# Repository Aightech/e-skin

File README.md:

# E-Skin

A bioinspired electronic skin system for robotic applications, combining FSR (force-sensing resistor) arrays and accelerometer arrays.

## Overview

The electronic board uses two multiplexers and two 16-channel ADCs to read the FSRs. The multiplexers select the row or column of the FSR array, while the ADCs read the sensor values. A Teensy 4.1 controls the multiplexers and ADCs and sends data to the computer via USB or Ethernet.

**Operation modes:**
- **Single mode**: Connect one FSR array with up to 32x32 sensors
- **Dual mode**: Connect two FSR arrays with up to 16x16 sensors each

**Sampling rate:** ~400 KHz/channel (1562.5 Hz for a 16x16 array)

## Project Structure

```
e-skin/
├── host/           # C++/Qt host application
│   ├── src/        # Source code (main.cpp)
│   └── lib/        # Git submodules (com_client, built_lsl)
├── src/            # Teensy firmware
│   └── Eskin/      # Main production firmware
├── models/         # KiCAD PCB designs
│   ├── KiCAD/              # Main control board (MUX + ADC)
│   ├── customSquare16x16/  # 16x16 FSR array
│   ├── customSquare8x8/    # 8x8 FSR array
│   ├── LIS2DH_array/       # LIS2DH accelerometer array
│   ├── KX134_array/        # KX134 accelerometer array
│   └── inskinacc/          # In-skin accelerometer
└── script/         # Python/MATLAB data acquisition scripts
```

## Requirements

### Host Application
- CMake 3.3+
- Qt6 (Core, Widgets, PrintSupport)
- C++11 compiler

### Firmware
- Arduino IDE or PlatformIO
- Teensy 4.1 board support

### Python Scripts
- Python 3.x
- Dependencies: `pip install -r script/requirements.txt`

## Building

### Host Application

```bash
cd host
mkdir build && cd build
cmake .. && make
./FSR_array -h  # Show usage
```

### Firmware

Upload `src/Eskin/Eskin.ino` to Teensy 4.1 using Arduino IDE or PlatformIO.

- Board: Teensy 4.1
- Port: `/dev/ttyACM0` (Linux) or `COMx` (Windows)

### Python Data Recorder

```bash
pip install -r script/requirements.txt
python script/record.py <port> <array_size>
# Example: python script/record.py /dev/ttyACM0 16
```

## Communication Protocol

- **Serial**: 500000 baud
- **Ethernet**: TCP port 5000
- **Command format**: 1 byte (2 MSB = mode, 6 LSB = array size)
  - Mode 0: Request 1 FSR array
  - Mode 1: Request 2 FSR arrays
  - Mode 2: Request 1 ACC array
  - Mode 3: Request 1 ACC array + 2 FSR arrays
- **Response**: 4-byte timestamps + uint16_t sensor data

## Submodule Dependencies

- [built_lsl](host/lib/built_lsl/README.md) - Lab Streaming Layer integration
- [com_client](host/lib/com_client/README.md) - Serial/TCP communication library

Initialize submodules:
```bash
git submodule update --init --recursive
```

## Example

See [main.cpp](host/src/main.cpp) for an example of how to use the communication library.

## Contributing

See [CONTRIBUTING.md](CONTRIBUTING.md) for details on our code of conduct and the process for submitting pull requests.

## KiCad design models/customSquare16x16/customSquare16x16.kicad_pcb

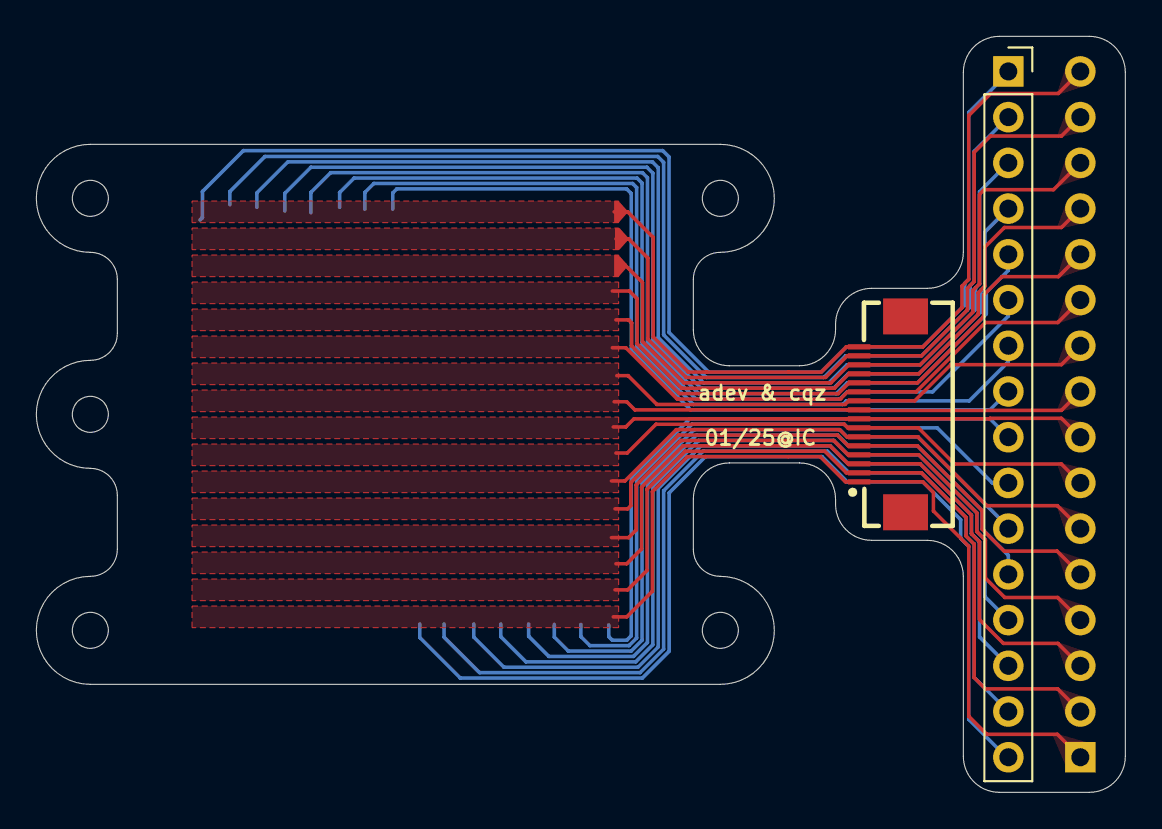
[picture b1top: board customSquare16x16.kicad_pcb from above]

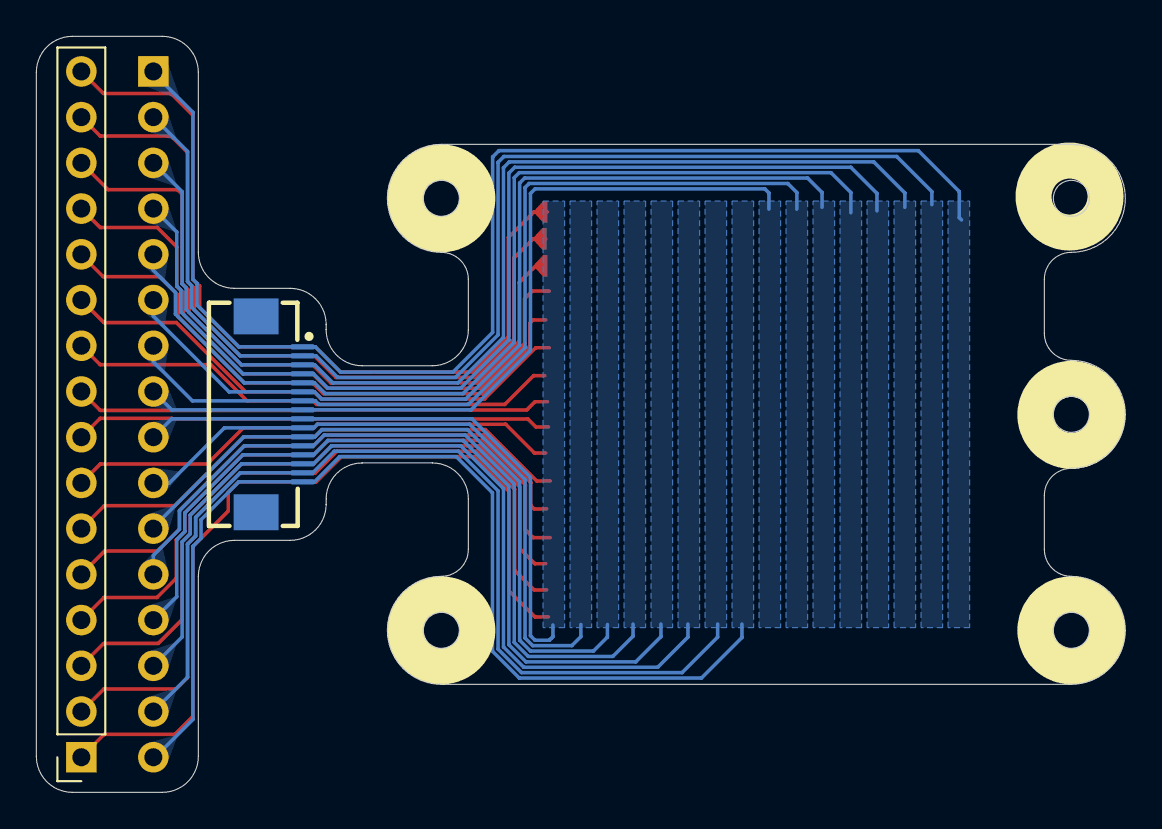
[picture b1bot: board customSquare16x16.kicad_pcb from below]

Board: 2 copper layers, 60.5 x 42.0 mm, 4 parts (2 on the bottom side), 32 nets.

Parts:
FPC1, FPC2: FPC-05F-16PH20; FPC-SMD_16P-P0.50_FPC-05F-16PH20
J1, J2: Conn_01x16_Pin; PinSocket_1x16_P2.54mm_Vertical

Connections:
/ain0: FPC2.1, J2.1
/ain1: FPC2.2, J2.2
/ain2: FPC2.3, J2.3
/ain3: FPC2.4, J2.4
/ain4: FPC2.5, J2.5
/ain5: FPC2.6, J2.6
/ain6: FPC2.7, J2.7
/ain7: FPC2.8, J2.8
/ain8: FPC2.9, J2.9
/ain9: FPC2.10, J2.10
/ain10: FPC2.11, J2.11
/ain11: FPC2.12, J2.12
/ain12: FPC2.13, J2.13
/ain13: FPC2.14, J2.14
/ain14: FPC2.15, J2.15
/ain15: FPC2.16, J2.16
/out0: FPC1.1, J1.1
/out1: FPC1.2, J1.2
/out2: FPC1.3, J1.3
/out3: FPC1.4, J1.4
/out4: FPC1.5, J1.5
/out5: FPC1.6, J1.6
/out6: FPC1.7, J1.7
/out7: FPC1.8, J1.8
/out8: FPC1.9, J1.9
/out9: FPC1.10, J1.10
/out10: FPC1.11, J1.11
/out11: FPC1.12, J1.12
/out12: FPC1.13, J1.13
/out13: FPC1.14, J1.14
/out14: FPC1.15, J1.15
/out15: FPC1.16, J1.16

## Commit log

2025-01-29 deploy: 081741f775edaccc05d8c0f96904bd5eb41160c2
2025-01-29 deploy: 1da3b2e9e8cf613343b81367af69af36bb8fbafe
2025-01-29 deploy: 69415a4cea2cdfe939ce7d985fec2f7f436548d2
2025-01-29 deploy: 27c3091dd386f0224adb989f3082aab685982569
2026-02-01 Update README with comprehensive documentation
    Add project structure, requirements, firmware upload instructions,
    Python script usage, and communication protocol details. Fix broken
    markdown link syntax.
2026-04-20 chore: rewrite .gitignore and stop tracking build artifacts
    Rewrite the whitelist-based .gitignore to:
    - add /host to the whitelist (it was fully ignored by /*)
    - drop stale root entries (bin, include, lib, tool_lib, CMakeLists.txt, etc.)
    - switch subtree whitelists from !/dir/* to !/dir/** so nested files are kept
    - re-ignore generated content inside whitelisted subtrees:
    build/, venv/, __pycache__, *.pyc, *-backups/, fp-info-cache,
2026-04-20 models(yl16x16): add p1 and p2 PCB projects
    New 16x16 FSR panel variants (yl16x16_p1, yl16x16_p2) with schematics,
    layouts, KiCAD project files, flex configuration, and fabrication jobset.
    Generated outputs (plots/, jlcpcb/, backups, fp-info-cache) are excluded
    by .gitignore.
2026-04-20 models(customSquare16x16): update PCB and project
2026-04-20 docs: add CLAUDE.md and MUXEDADC plot2.py
    - CLAUDE.md: project guidance for Claude Code (build commands, code
    style, architecture overview)
    - src/MUXEDADC/plot2.py: live-plot variant for the muxed ADC sketch
2026-05-07 springy model
